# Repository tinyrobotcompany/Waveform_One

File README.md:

# Waveform One

A music-reactive 64×32 HUB75 LED display with a touchscreen and local phone
remote. The current P4 configuration uses the Waveshare
ESP32-P4-WIFI6-Touch-LCD-7B, onboard ES7210 audio capture and direct P4 LED drive.
It joins home Wi-Fi and uses ACRCloud for music identification. The retired Raspberry Pi runtime and its release artifacts have been removed.
Standalone S3 hardware test programs remain for bench testing.

Public source and local audio processing are foundations for long-term ownership.
Cloud song identification still requires ACRCloud. A repeatable recognition
accuracy benchmark and a documented cold-boot offline demonstration are pending;
see the evidence and acceptance plans below rather than assuming a measured
accuracy percentage or a complete offline guarantee.

## Licence and independent maintenance

Original software is licensed under [Apache 2.0](LICENSE). Original hardware and mechanical designs are licensed under [CERN-OHL-W 2.0](LICENSES/CERN-OHL-W-2.0.txt). See [licensing scope and third-party exclusions](LICENSING.md). These licences allow independent maintenance and commercial use; they do not provide recognition-service accounts or rights to our trademarks.

## Documentation

- [Wiring, firmware programs and build instructions](firmware/esp32/README.md)
- [ESP32-P4 display bring-up and wiring](firmware/esp32/p4_display/README.md)
- [ESP32-P4 controller architecture decision](docs/architecture/0001-esp32-p4-display-controller.md)
- [Contributing and local tests](CONTRIBUTING.md)
- [Release notes](CHANGELOG.md)
- [Native P4 over-the-air updates](docs/p4-ota.md)
- [Recognition accuracy protocol and result template](docs/validation/recognition-protocol.md)
- [Recognition providers and commercial-cost review](docs/product/recognition-commercial-review.md)
- [Offline visualizer acceptance plan](docs/validation/offline-visualizer.md)
- [Ownership and service continuity](docs/product/longevity.md)
- [Buyer-readiness checklist](https://github.com/tinyrobotcompany/Waveform_One/issues/25)
- [CI and releases](docs/delivery.md)
- [Wi-Fi and QR phone setup](docs/setup.md)
- [HTTPS identity provisioning and renewal](docs/secure-phone-access.md)
- [Managed certificate migration plan and accepted decisions](docs/plans/managed-certificates.md)
- [Agent in Chief working protocol](docs/engineering-agent-protocol.md)
- [Production secure boot and encrypted credentials](docs/production-security.md)

Native P4 signed updates follow Tempo: monthly checks, an overnight installation
window, countdown and postponement, with controls on the touchscreen and paired phone.
The P4 needs a one-time USB bootstrap into the A/B layout before OTA updates.

<!-- privacy-notice:start -->
## Microphone and privacy

**Waveform One does not save audio recordings on the device.** Automatic music
recognition is a core feature and runs during normal operation. This notice
describes the current ESP32-P4 firmware; temporary audio capture and transmission
for recognition are different from saving a permanent recording.

**What the microphone captures.** While powered on and running with capture enabled,
the microphone continuously captures nearby sound to animate the LEDs and identify music. Audio
is processed in temporary RAM, including a rolling 16-second buffer. Buffers are
reused; this is not a recording archive or a guarantee that every temporary copy
is securely erased after exactly 16 seconds. Waveform One does not provide
conversation transcription or a feature for replaying recorded conversations.

**What leaves the device.** For recognition, the P4 sends actual audio clips of
up to 10 seconds directly to ACRCloud over HTTPS, not to a Waveform One audio-storage
server. Requests can repeat approximately every 2.5 seconds while recognition is
active, so clips overlap substantially. Requests also include an account access-key
identifier, request timestamp and authentication signature; the service can see
the connecting network's public IP address. The access secret is used locally to
sign requests, rather than sent as an audio-request field.

**Nearby voices.** Clips may include nearby voices and other background sounds.
Sound classification cannot guarantee that speech is excluded, and sustained
unclassified sound can also trigger a recognition request. Do not assume that
only music leaves the device. People nearby should be made aware that automatic
music recognition can send samples containing their voices to ACRCloud.

**Provider processing and retention.** ACRCloud states that temporary raw audio
is deleted when request processing succeeds or fails, without a retained audio
archive or long-term audio backup. Recognition results, fingerprints, request
records and technical logs have separate retention and deletion rules; they are
not all deleted with the audio. Processing location depends on the ACRCloud
project's configured region. See [ACRCloud's data-processing terms](https://www.acrcloud.com/dpa/)
and [privacy policy](https://www.acrcloud.com/privacy/). These are the
provider's commitments, not a claim that Waveform One independently verifies
server-side deletion. Requests about provider-held data should follow the
applicable account's ACRCloud privacy and deletion procedures.

**Other stored information.** Device diagnostics include recognised titles,
artists, timings and sound levels, and can be retained when captured by a
connected development computer. Recognition metadata and artwork may be cached
for display. ACRCloud credentials are stored on the device so recognition
continues after firmware updates; that credential storage is separate from audio
buffering. Using your own ACRCloud account changes whose account is used, not
whether recognition audio is transmitted to ACRCloud.

**Optional listening history and sharing.** On firmware offering listening history,
collection starts disabled after every restart. Enabling it stores up to 50 recent
recognised tracks and timing metadata in device RAM; it stores no audio. Paired
phones can view, export or delete this history. Disabling it or restarting clears
the device history, but does not delete exported files. The optional desktop
Last.fm bridge sends eligible track metadata and timestamps only after the owner
authorises their account and explicitly submits an export. It stores account
credentials and a bounded submission queue on that computer with private file
permissions, without encryption. Deleting local files does not delete Last.fm's
records; use Last.fm's account controls. Discogs links open a search only when
clicked and disclose the search terms and normal browser/network information to
Discogs. Neither integration uploads microphone audio.

**Owner account controls.** On firmware offering owner account setup, credentials
are entered on the touchscreen, not through the phone's unencrypted local HTTP
connection. Replacing or disabling an account takes effect after restart; recognition
can continue with the previous account until then. Disabling the account stops
cloud recognition after restart but leaves local microphone processing active.
Wi-Fi/pairing/account settings persist in device storage, which is not newly
encrypted by these features. Removal is not a claim of forensic secure erasure.

**Stopping capture.** Powering off Waveform One stops microphone capture and
uploads. Disconnecting its internet connection prevents cloud recognition
requests from reaching ACRCloud, but does not itself turn off the microphone.
On firmware with Settings → Microphone, the touchscreen mute pauses local P4
capture, clears capture buffers, invalidates old audio/results and inhibits new
recognition requests. The paired phone shows the muted state. A successfully
saved mute survives normal restart and application OTA; an erased/reset settings
partition restores the fresh-device default of listening. If saving fails, mute
still takes effect now, but the screen warns that the previous saved setting may
return after restart. Unmute requires a successful save; corrupt/unreadable
settings default to muted without erasing storage.

This is a software mute: the microphones remain electrically connected and may
remain powered. It is not a physical privacy switch or a guarantee against
replacement/malicious firmware. Microphone-reactive LEDs also stop receiving
sound while muted. An already-running capture read is discarded when it returns;
an in-progress network operation may finish before cancellation is observed.
Cancelled uploads are closed and not retried, but bytes already sent cannot be
recalled. No switch installation, GPIO wiring or microphone modification is
required. The control covers the local P4 capture path, not a separately running
legacy S3 microphone controller.
<!-- privacy-notice:end -->

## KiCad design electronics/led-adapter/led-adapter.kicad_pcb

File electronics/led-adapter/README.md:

# LED adapter board

A small board (94 × 44 mm) that connects the P4 touchscreen board to the LED
panel, so the P4 can drive the panel without the ESP32-S3 and without loose
jumper wires. It is also the system's one power point: the 5 V supply plugs in
here, and the board powers the LED panel and the P4. Every cable plugs in at
both ends.

```text
5 V supply (barrel plug) ── J5 ┬── J4 ──[panel's own power cable]── LED panel power
                               ├── J6 ──[USB-C to USB-C cable]────── P4 USB-C port
                               └── buffers, power LED
P4 socket P3 ──[PH2.0 12-pin cable, as delivered]── J1 ┐
                                                       ├─ buffers ── J3 ──[panel's grey ribbon]── LED panel input
P4 socket P1 ──[PH2.0 12-pin cable, as delivered]── J2 ┘
```

| Connector | Takes |
|---|---|
| J1 | Cable to the P4's **P3** socket (GPIO2–5, 28–31, 34; 3.3 V and GND) |
| J2 | Cable to the P4's **P1** socket (GPIO49–52; GND) |
| J3 | The LED panel's own 16-pin ribbon (HUB75) |
| J4 | The LED panel's own power cable (screw terminal, up to 4 A) |
| J5 | The 5 V supply's barrel plug (5.5 × 2.1 mm, centre +) |
| J6 | USB-C to USB-C cable to the P4's USB-C port (power only) |

The labels are printed on the board. D2, marked POWER, lights while 5 V is
present.

## In the case

The board lies flat on four floor posts (M3 heat-set inserts, 5 mm high) in
the left half, behind the screen and under the P4's two 12-pin sockets, with
J1 and J2 towards the back. `board.json` gives its position (`case_left_x`,
`case_rear_y`, `standoff_height`); the casing CAD reads it from
`placement.json`, as it does for the carrier board.

## What is on it

- **One power input, J5**, for a 5 V supply of at least 6 A: up to 4 A for
  the panel and the rest for the P4. MEAN WELL GST60A05-P1J (5 V, 6 A,
  5.5 × 2.1 mm plug, centre +) fits. A TVS diode (D1) clamps plug-in spikes.
- **The panel's power, J4**, straight from J5 on wide copper.
- **The P4's power, J6**, through a 2.5 A resettable fuse (F1). Waveshare
  documents USB-C (or a battery) as the P4's only power inputs, so the board
  feeds it like a USB charger: 56 kΩ on CC1 and CC2 mark it as a USB power
  source. The P4's two USB-C ports each have their own input diode, so the
  Mac can stay plugged into the P4's other USB-C port for flashing.
- **Two 74AHCT245 buffers** turn the P4's 3.3 V signals into the 5 V the
  panel expects. These are the same buffers as on the carrier board.
- **The panel stays dark unless the P4 is on.** Q1 enables the buffers only
  while the P4's 3.3 V is present. Otherwise R4 holds the panel's OE high.
  R1 does the same while the P4 starts.

The signal map is Codex's, from
`docs/commissioning/2026-10-14-p4-led-takeover.md`:

| HUB75 | R1 | G1 | B1 | R2 | G2 | B2 | A | B | C | D | CLK | LAT | OE |
|---|---|---|---|---|---|---|---|---|---|---|---|---|---|
| P4 GPIO | 2 | 3 | 4 | 5 | 28 | 29 | 30 | 31 | 34 | 49 | 52 | 50 | 51 |

The P4's socket pins come from Waveshare's 7B schematic (P1 and P3).
`tools/netlist.py` lists them pin by pin.

## Cables

### The two 12-pin cables: use them as delivered

J1 and J2 take PH2.0 12-pin double-ended cables **exactly as they come from
the bag**: the AliExpress "Double head, 12P, 20CM" cables. Don't move any wire.

Those cables are crossed: pin 1 at one end is wired to pin 12 at the other.
Revision 2 makes the cross-over on the board instead. J1 and J2 pin *n*
carries the P4 socket's pin 13 − *n*:

| P4 P3 pin | P3 label | J1 pin | | P4 P1 pin | P1 label | J2 pin |
|---|---|---|---|---|---|---|
| 1 | IO36 | 12 (unused) | | 1 | IO52 (CLK) | 12 |
| 2 | IO34 (C) | 11 | | 2 | IO51 (OE) | 11 |
| 3 | IO31 (B) | 10 | | 3 | IO50 (LAT) | 10 |
| 4 | IO30 (A) | 9 | | 4 | IO49 (D) | 9 |
| 5 | IO29 (B2) | 8 | | 5–7 | IO48–46 | 8–6 (unused) |
| 6 | IO28 (G2) | 7 | | 8 | GND | 5 |
| 7 | IO5 (R2) | 6 | | 9 | VO4 | 4 (unused) |
| 8 | IO4 (B1) | 5 | | 10 | 3V3 | 3 (unused) |
| 9 | IO3 (G1) | 4 | | 11 | GND | 2 |
| 10 | IO2 (R1) | 3 | | 12 | BAT | 1 (unused) |
| 11 | GND | 2 | | | | |
| 12 | 3V3 | 1 | | | | |

How we know: the owner's photos of the cables plugged in unmodified
(2026-11-04). At the P4's P3 socket, from IO36 to 3V3, the wires run red,
black, brown, grey, purple, blue, green, orange, yellow, white, red, black.
At revision 1's J1, from pin 1 (the end nearest J4) to pin 12, they ran in
exactly the opposite order. The P1 cable is the same.

**Check before plugging in: follow each cable, don't go by colour.** The two
cables are identical, with the same colours, so a cable plugged into the
wrong board socket looks just like a right one. Trace each cable by hand from
end to end:

- from the P4's **P3** socket (pins labelled 3V3, GND, IO2 … IO36) to **J1**,
  printed "to P4 socket P3";
- from the P4's **P1** socket (pins labelled BAT, GND, 3V3, VO4 … IO52) to
  **J2**, printed "to P4 socket P1".

The cables themselves are never modified. In the working setup (photo,
2026-11-17) the two cables cross over each other between the P4 and the
green board: that crossing is what puts each cable in its own socket. If the
two cables run side by side without crossing, check them again.

If the two cables are in each other's sockets at the green board, the POWER
LED lights and the P4 starts, but the panel stays dark. Swap the two plugs at
the green board, without changing the cables. (This happened at the first revision 2 bring-up,
2026-11-17; after the swap the panel worked with the cables as delivered.)
Don't leave them swapped: J1 pin 1, the board's 3.3 V input, then gets the
P4's BAT pin.

The two cables reworked by hand for revision 1 (wires moved to run pin 1 to
pin 1) do **not** work on revision 2. Keep them with the revision 1 board.

### Power

- **5 V supply**: 5 V, at least 6 A, barrel plug 5.5 × 2.1 mm, centre +. For
  example MEAN WELL GST60A05-P1J (it needs an IEC C13 mains lead, sold
  separately).
- **USB-C to USB-C cable**, short (about 20 cm), from J6 to the P4's USB-C
  port. Any charging cable works: only power goes through it.
- **The panel's own power cable** into J4: red to **+5V**, black to **GND**,
  as printed.

### Panel signals

- The panel's grey 16-pin ribbon, which came with the panel, into J3 and the
  panel's **input** socket.

## Order from JLCPCB

```sh
python3 electronics/led-adapter/tools/export_jlc.py
```

This writes `fab/`. On jlcpcb.com, follow the carrier board's steps
(`electronics/carrier/README.md`, "Order from JLCPCB"):

1. Upload `led-adapter-gerbers.zip`. Use the defaults: 2 layers, 1.6 mm,
   quantity 5.
2. Turn on PCB Assembly, top side. J1–J5 are through-hole, so choose
   **Standard** assembly with through-hole soldering.
3. Upload `led-adapter-bom.csv` and `led-adapter-cpl.csv`. Check that every
   part is matched and in stock.
4. In the placement preview, check that each part sits the right way round.
   Compare it with KiCad's render (`kicad-cli pcb render --side top`):
   - pin 1 of U1, U2, Q1, D1, D2, J1, J2 and J3;
   - the wire entries of J4, which face the board's front edge (away from the
     "+5V" and "GND" text), so the wires come in from the front as the case
     expects;
   - the plug opening of J5, at the board's rear edge (next to J1), and the
     mouth of J6, at the board's left edge.

   Rotate any part that is wrong in JLCPCB's preview. Revision 1 was ordered
   with J4 turned the other way, and JLCPCB was asked to turn it 180° (2026-10-20);
   these files now have it the right way round.

## Regenerate

The tools reuse the carrier board's generators (`reuse.py` points them at this
folder). Don't edit the generated files by hand. Edit `tools/netlist.py` or
`board.json` instead, then run:

```sh
python3 electronics/led-adapter/tools/gen_schematic.py
KP=/Applications/KiCad/KiCad.app/Contents/Frameworks/Python.framework/Versions/Current/bin/python3
$KP electronics/led-adapter/tools/build_board.py
$KP electronics/led-adapter/tools/route_board.py      # needs Java and Freerouting, as for the carrier
K=/Applications/KiCad/KiCad.app/Contents/MacOS/kicad-cli
$K sch erc electronics/led-adapter/led-adapter.kicad_sch
$K pcb drc --schematic-parity electronics/led-adapter/led-adapter.kicad_pcb
```

## Status

- **Revision 2** (this design): one power point, power LED, cables used as
  delivered. Designed, routed and checked: no design-rule violations,
  nothing unconnected, and the board matches the schematic. Every panel
  signal was traced from the P4 pin, through an as-delivered cable, to the
  HUB75 pin. **Ordered 2026-11-14** from JLCPCB, 5 assembled boards
  (order Y4-13817483A). J6 was fitted as LCSC C3020560, the same GCT
  USB4105-GF-A, because C3025063 was out of stock.
  **Working on hardware 2026-11-17**: P4 powered from J6 and the panel
  lit, with both 12-pin cables as delivered.
- **Revision 1** (ordered 2026-10-20, in use): needs the 12-pin cables
  reworked to run pin 1 to pin 1, takes 5 V for the buffers only on J4, and
  the P4 is powered separately by USB-C.
- Revision 2 is 22 mm wider on the left than revision 1; the parts from
  revision 1 sit at the same places in the case. The casing CAD follows
  `placement.json`: rebuild the case before printing it for revision 2.

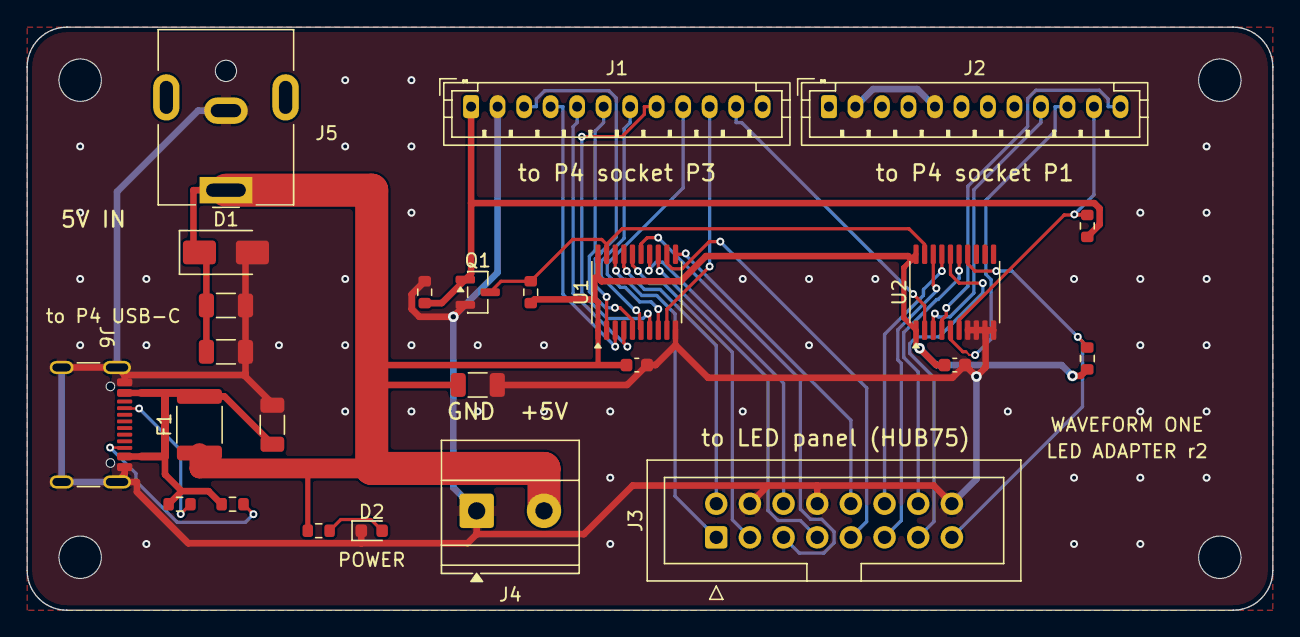
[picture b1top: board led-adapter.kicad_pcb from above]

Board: 2 copper layers, 94.0 x 44.0 mm, 29 parts (0 on the bottom side), 34 nets.

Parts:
C1, C2: 100nF; C_0603_1608Metric
C3, C4, C5, C6: 22uF 10V; C_1206_3216Metric
D1: SMAJ5.0A; D_SMA
D2: Green; LED_0603_1608Metric
F1: 2.5A hold; Fuse_1812_4532Metric
H1, H2, H3, H4: M3; MountingHole_3.2mm_M3
J1, J2: PH2.0 12-pin; JST_PH_B12B-PH-K_1x12_P2.00mm_Vertical
J3: HUB75; IDC-Header_2x08_P2.54mm_Vertical
J4: 5V to LED panel; TerminalBlock_Phoenix_MKDS-1,5-2-5.08_1x02_P5.08mm_Horizont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
J5: PJ-063AH; BarrelJack_CUI_PJ-063AH_Horizontal
J6: 5V to P4; USB_C_Receptacle_GCT_USB4105-xx-A_16P_TopMnt_Horizontal
Q1: 2N7002; SOT-23
R1, R3, R4: 10k; R_0603_1608Metric
R2: 100k; R_0603_1608Metric
R5, R6: 56k; R_0603_1608Metric
R7: 1k; R_0603_1608Metric
U1, U2: 74AHCT245; TSSOP-20_4.4x6.5mm_P0.65mm

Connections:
/+5V: C1.1, C2.1, C3.1, C4.1, C5.1, D1.1, F1.1, J4.2, J5.1, R3.1, R4.1, R7.1, U1.1, U1.20, U2.1, U2.20
/BUF_EN: Q1.3, R3.2, U1.19, U2.19
/GND: C1.2, C2.2, C3.2, C4.2, C5.2, C6.2, D1.2, D2.1, J1.2, J2.2, J2.5, J3.4, J3.8, J3.16, J4.1, J5.2, J6.A1, J6.A12, J6.B1, J6.B12, J6.SH, Q1.2, R2.2, U1.10, U2.7, U2.8, U2.9, U2.10
/HUB_A: J3.9, U1.12
/HUB_B: J3.10, U1.11
/HUB_B1: J3.3, U1.16
/HUB_B2: J3.7, U1.13
/HUB_C: J3.11, U2.18
/HUB_CLK: J3.13, U2.16
/HUB_D: J3.12, U2.17
/HUB_G1: J3.2, U1.17
/HUB_G2: J3.6, U1.14
/HUB_LAT: J3.14, U2.15
/HUB_OE: J3.15, R4.2, U2.14
/HUB_R1: J3.1, U1.18
/HUB_R2: J3.5, U1.15
/LED_5V: D2.2, R7.2
/P4_3V3: J1.1, Q1.1, R1.1, R2.1
/P4_5V: C6.1, F1.2, J6.A4, J6.A9, J6.B4, J6.B9, R5.1, R6.1
/P4_A: J1.9, U1.8
/P4_B: J1.10, U1.9
/P4_B1: J1.5, U1.4
/P4_B2: J1.8, U1.7
/P4_C: J1.11, U2.2
/P4_CC1: J6.A5, R5.2
/P4_CC2: J6.B5, R6.2
/P4_CLK: J2.12, U2.4
/P4_D: J2.9, U2.3
/P4_G1: J1.4, U1.3
/P4_G2: J1.7, U1.6
/P4_LAT: J2.10, U2.5
/P4_OE: J2.11, R1.2, U2.6
/P4_R1: J1.3, U1.2
/P4_R2: J1.6, U1.5

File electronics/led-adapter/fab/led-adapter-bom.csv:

Comment,Designator,Footprint,LCSC Part #
PH2.0 12-pin,"J1,J2",JST_PH_B12B-PH-K_1x12_P2.00mm_Vertical,C158028
10k,"R1,R3,R4",R_0603_1608Metric,C25804
2N7002,Q1,SOT-23,C8545
100k,R2,R_0603_1608Metric,C25803
74AHCT245,"U1,U2",TSSOP-20_4.4x6.5mm_P0.65mm,C173388
100nF,"C1,C2",C_0603_1608Metric,C14663
HUB75,J3,IDC-Header_2x08_P2.54mm_Vertical,C492443
5V to LED panel,J4,"TerminalBlock_Phoenix_MKDS-1,5-2-5.08_1x02_P5.08mm_Horizontal",C480516
PJ-063AH,J5,BarrelJack_CUI_PJ-063AH_Horizontal,C22434582
SMAJ5.0A,D1,D_SMA,C78401
22uF 10V,"C3,C4,C5,C6",C_1206_3216Metric,C12891
1k,R7,R_0603_1608Metric,C21190
Green,D2,LED_0603_1608Metric,C12624
2.5A hold,F1,Fuse_1812_4532Metric,C19078727
5V to P4,J6,USB_C_Receptacle_GCT_USB4105-xx-A_16P_TopMnt_Horizontal,C3025063
56k,"R5,R6",R_0603_1608Metric,C23206

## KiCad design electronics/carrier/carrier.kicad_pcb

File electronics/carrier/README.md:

# Carrier board

The board inside the cabinet that carries the ESP32-S3, drives the LED panel,
connects the microphone and shares out power. See [SPEC.md](SPEC.md).

Designed in KiCad 10. Placement is generated from `board.json`, which is the
single source for the outline, mounting holes and connector positions. The
casing CAD reads the same file.

## Rebuild the board placement

```sh
/Applications/KiCad/KiCad.app/Contents/Frameworks/Python.framework/Versions/Current/bin/python3 \
    electronics/carrier/tools/build_board.py
```

## Route

```sh
/Applications/KiCad/KiCad.app/Contents/Frameworks/Python.framework/Versions/Current/bin/python3 \
    electronics/carrier/tools/route_board.py
```

Needs Java and Freerouting 2.4.1 (`FREEROUTING_JAR`). It replaces all copper:
it draws the fixed tracks in `route_board.py`, autoroutes the rest, pours
ground and stitches it, and reports what is left unconnected. Rerun it after
every `build_board.py`.

## Order from JLCPCB

```sh
python3 electronics/carrier/tools/export_jlc.py
```

This writes `fab/`: `carrier-gerbers.zip` (the board), `carrier-bom.csv`
(parts with LCSC numbers, from `LCSC` in `netlist.py`) and `carrier-cpl.csv`
(part positions). Not-fitted parts are left out. On jlcpcb.com:

1. Upload `carrier-gerbers.zip`. Keep the defaults: 2 layers, 1.6 mm,
   1 oz copper, HASL lead-free (or ENIG), quantity 5.
2. Turn on PCB Assembly: top side, assemble 5 boards. The through-hole
   connectors (J1, J4, J5, J6) need Standard assembly with through-hole
   soldering, not Economic.
3. Upload `carrier-bom.csv` and `carrier-cpl.csv`. Check every part is
   matched and in stock.
4. In the placement preview, check each polarised part sits the right way
   round: pin 1 of U1, U4, U5, U6, U7 and J7; the stripe of D1; the green LED
   D2; the + of C1; and that each connector faces the board edge it should.
   JLCPCB's part models can be rotated from KiCad's; rotate any that are
   wrong there.

## Check and preview

```sh
K=/Applications/KiCad/KiCad.app/Contents/MacOS/kicad-cli
$K pcb drc --severity-all -o /tmp/carrier-drc.txt electronics/carrier/carrier.kicad_pcb
$K pcb render --side top -o /tmp/carrier-top.png electronics/carrier/carrier.kicad_pcb
```

## Design source

`tools/netlist.py` holds the circuit: every part, value, footprint and pin net.
Two generators read it:

- `tools/gen_schematic.py` writes `carrier.kicad_sch`. Any Python 3.9+ runs it.
- `tools/build_board.py` writes `carrier.kicad_pcb`, with every pad on its net,
  and `placement.json`. It needs KiCad's Python.

Do not edit the generated files by hand. Change `netlist.py`, `board.json` or
the fixed copper in `route_board.py` and regenerate:

```sh
python3 electronics/carrier/tools/gen_schematic.py
KP=/Applications/KiCad/KiCad.app/Contents/Frameworks/Python.framework/Versions/Current/bin/python3
$KP electronics/carrier/tools/build_board.py
$KP electronics/carrier/tools/route_board.py
K=/Applications/KiCad/KiCad.app/Contents/MacOS/kicad-cli
$K sch erc electronics/carrier/carrier.kicad_sch
$K pcb drc --schematic-parity electronics/carrier/carrier.kicad_pcb
```

## Status

Revision 1 is placed and routed.

- Schematic: passes the electrical rules check. The only warnings are the
  three intentional ties of unused buffer inputs to ground.
- Board: matches the schematic exactly, and passes the design-rule check with
  no errors and nothing unconnected. Four warnings remain: the silkscreen
  outlines of the USB-A socket (J4) and the LED power terminal (J6) overhang
  the board edge, as those connectors do by design. A fifth flags that the
  S3 module's footprint differs from KiCad's library: its ground-pad holes
  are drilled 0.3 mm instead of 0.2 mm, so every hole on the board is a
  standard drill size at JLCPCB.
- Chip resistor and capacitor references are left off the silkscreen (too
  dense); they remain on the fabrication layer.
- The USB-C power parts are marked do-not-populate. Their layout is complete
  but provisional; see SPEC.md before fitting them.

Library warnings in `kicad-cli` mean KiCad's global library tables are not set
up yet. Opening KiCad once creates them.

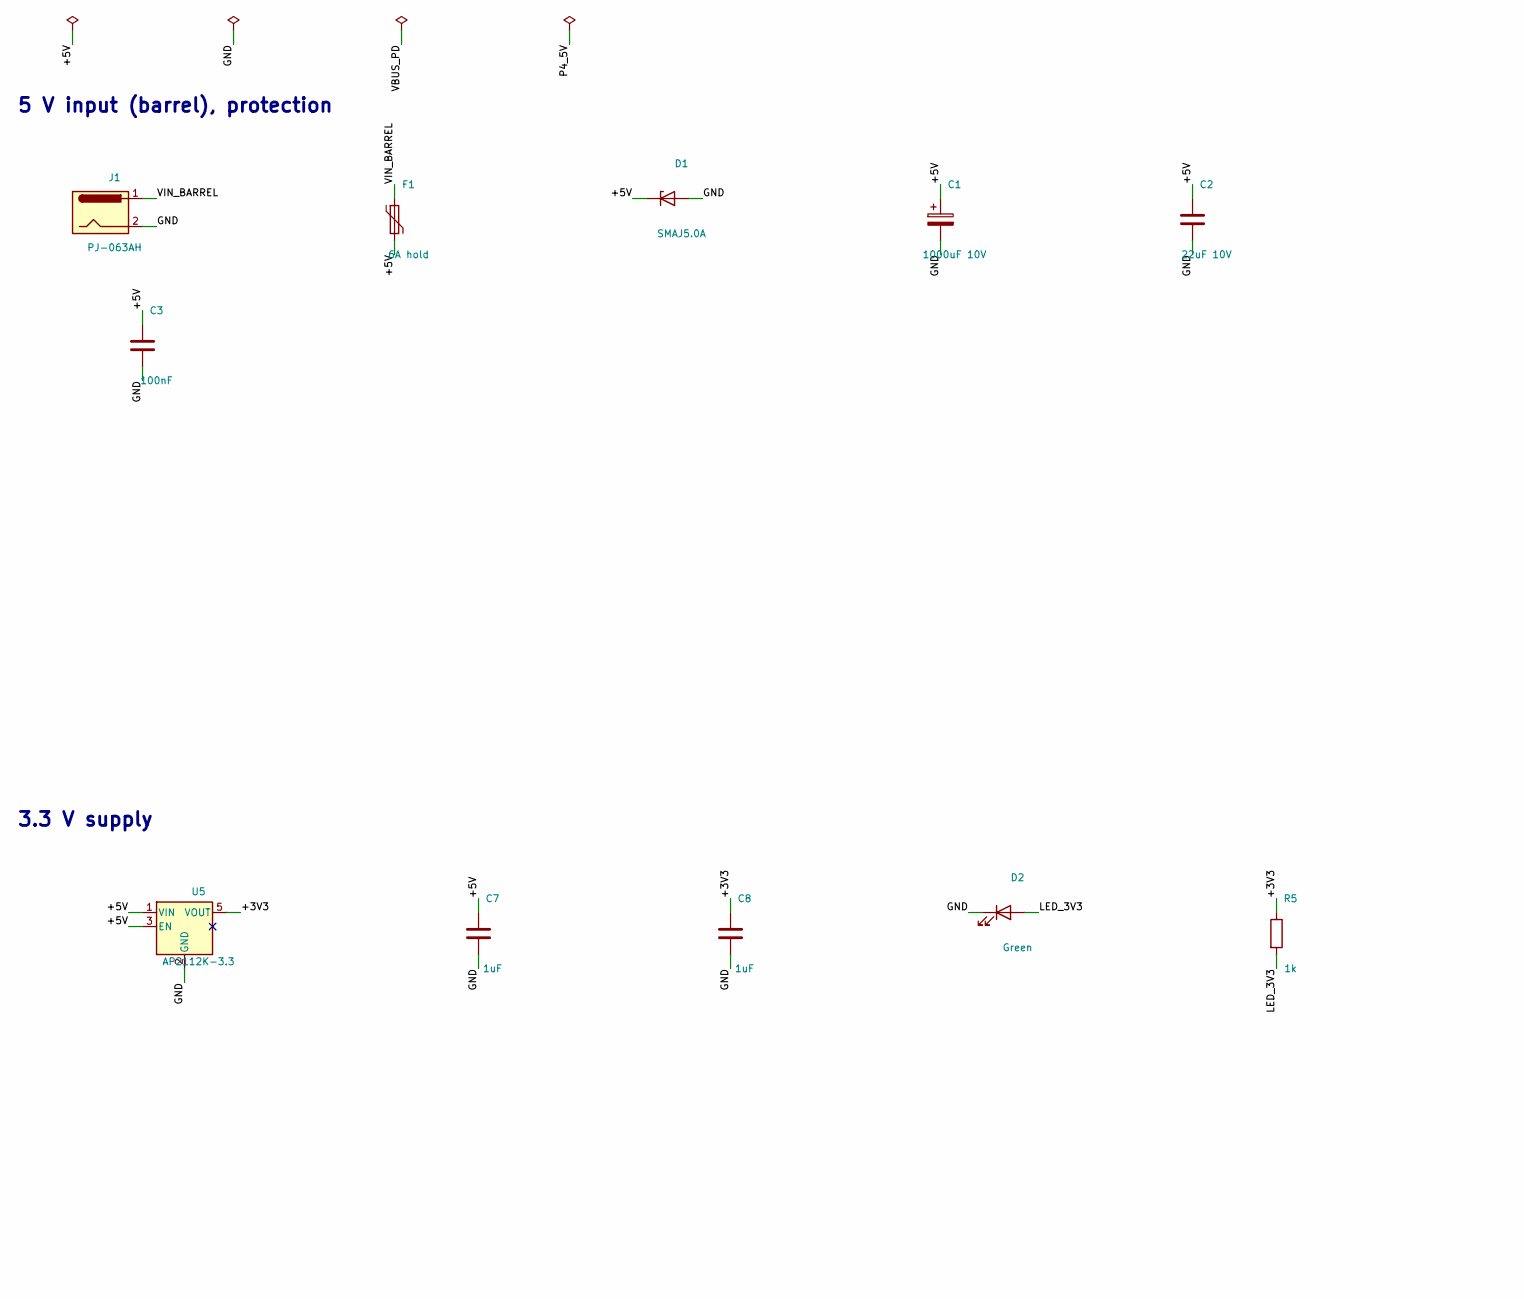
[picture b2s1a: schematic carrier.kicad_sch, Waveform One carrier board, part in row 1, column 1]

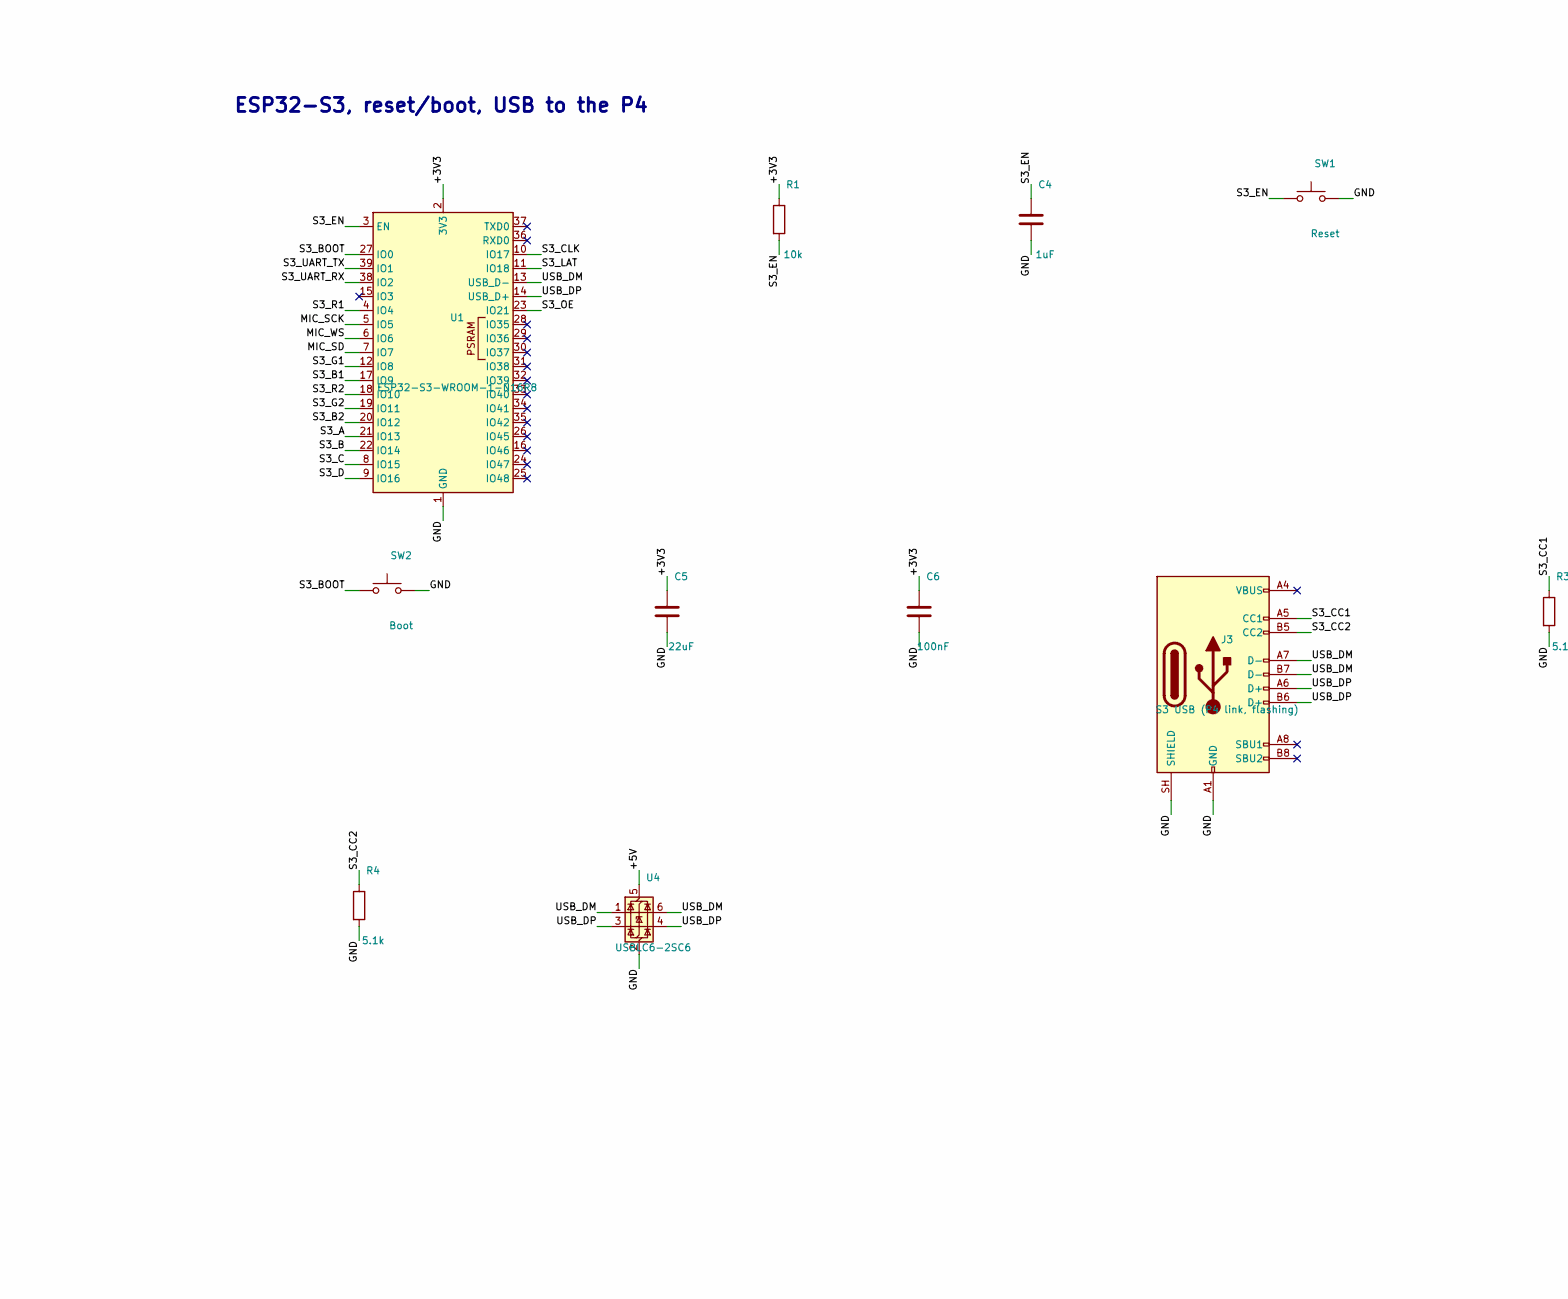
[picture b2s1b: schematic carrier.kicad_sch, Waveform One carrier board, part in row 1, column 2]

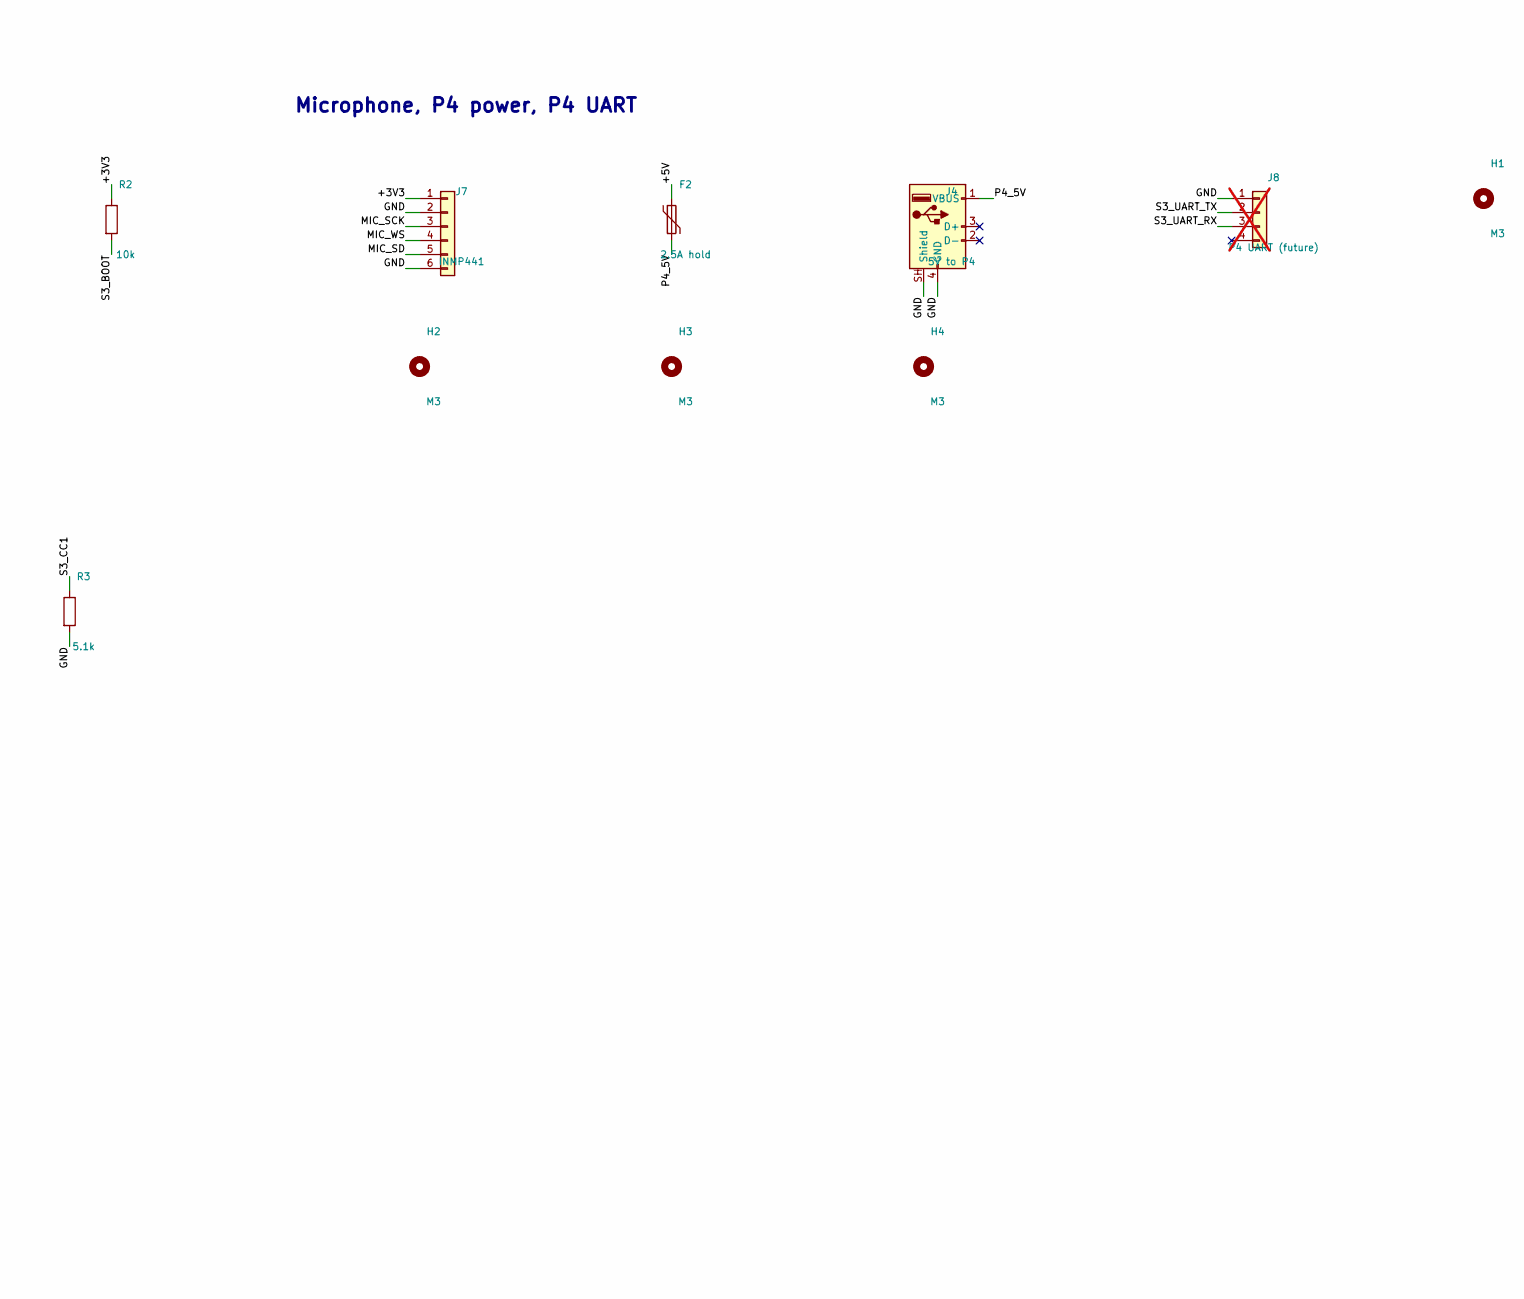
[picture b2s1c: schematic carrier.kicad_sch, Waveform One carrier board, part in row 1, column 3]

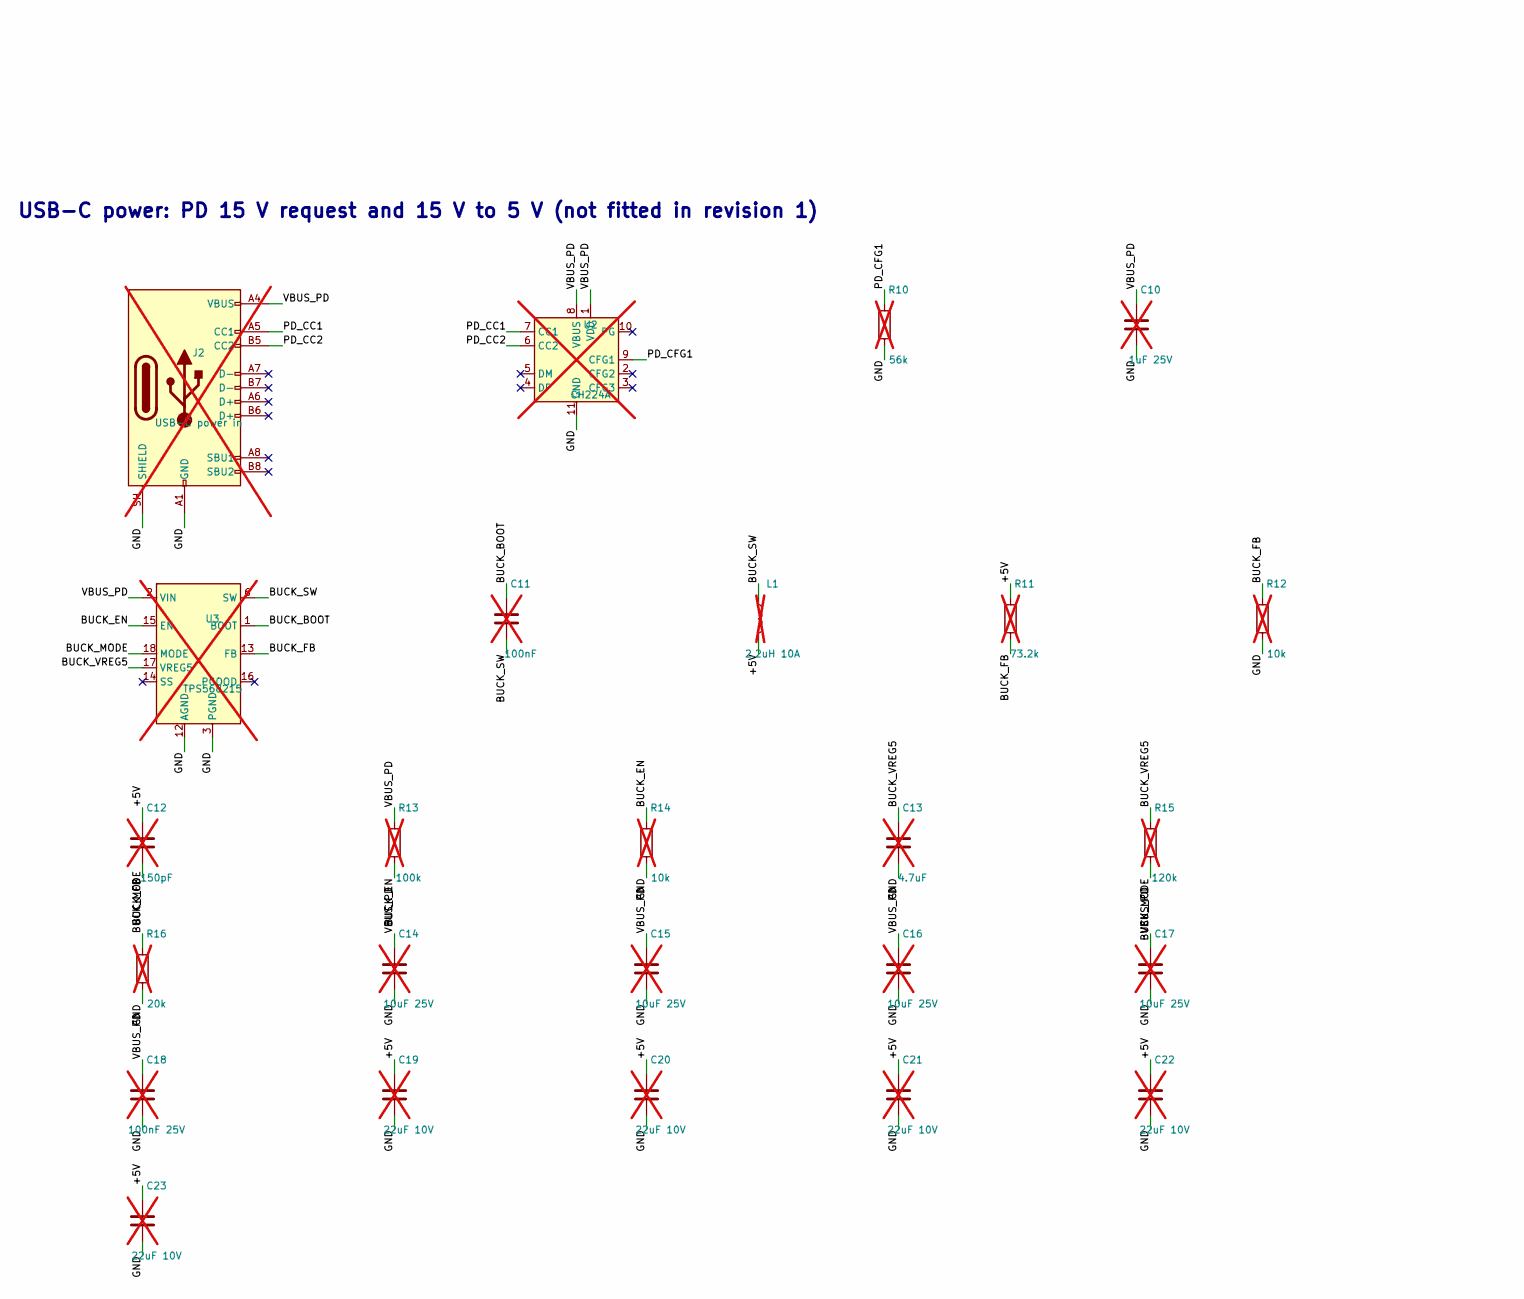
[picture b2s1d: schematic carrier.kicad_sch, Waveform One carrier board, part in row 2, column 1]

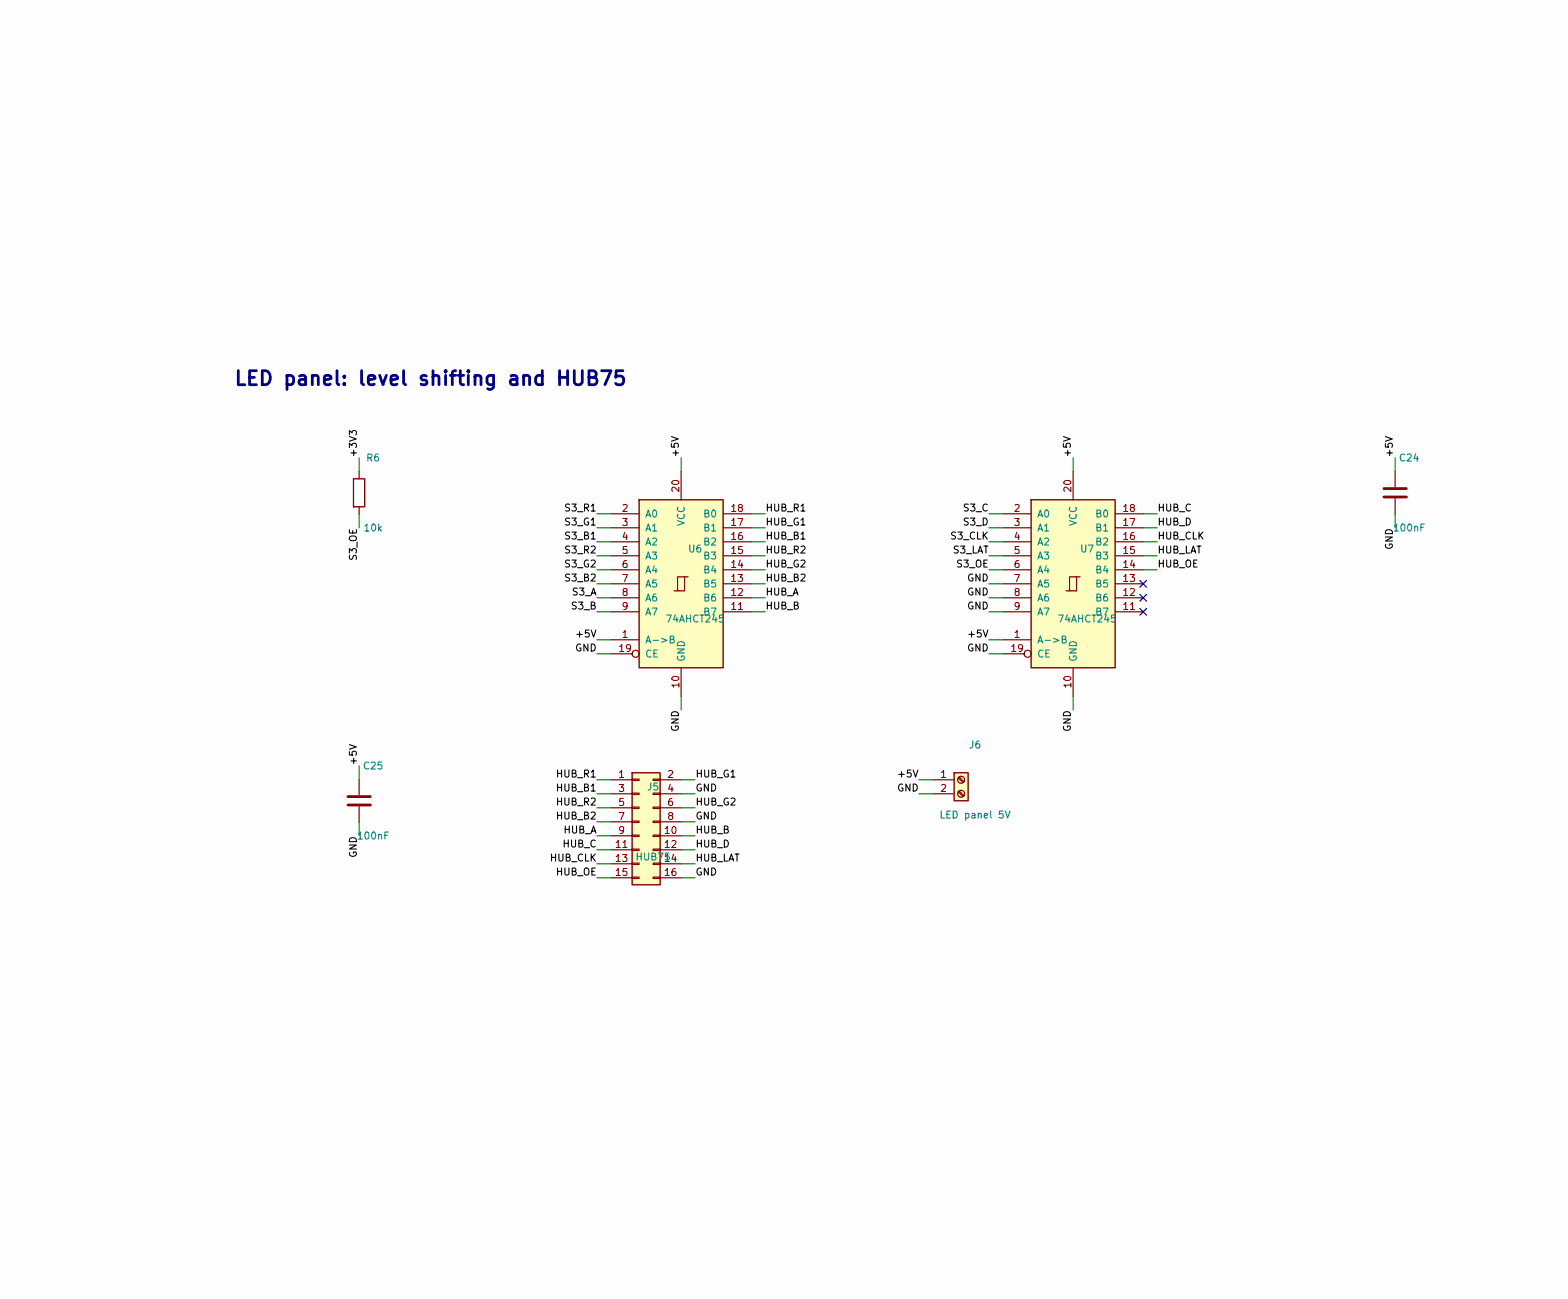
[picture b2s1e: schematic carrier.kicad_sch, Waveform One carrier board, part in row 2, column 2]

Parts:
C1: 1000uF 10V; CP_Elec_10x10.5
C2: 22uF 10V; C_1206_3216Metric
C3, C6, C24, C25: 100nF; C_0603_1608Metric
C4, C7, C8: 1uF; C_0603_1608Metric
C5: 22uF; C_1206_3216Metric
C10: 1uF 25V; C_0805_2012Metric; not fitted
C11: 100nF; C_0603_1608Metric; not fitted
C12: 150pF; C_0603_1608Metric; not fitted
C13: 4.7uF; C_0805_2012Metric; not fitted
C14, C15, C16, C17: 10uF 25V; C_1206_3216Metric; not fitted
C18: 100nF 25V; C_0603_1608Metric; not fitted
C19, C20, C21, C22, C23: 22uF 10V; C_1206_3216Metric; not fitted
D1: SMAJ5.0A; D_SMA
D2: Green; LED_0603_1608Metric
F1: 6A hold; Fuse_2920_7451Metric
F2: 2.5A hold; Fuse_1812_4532Metric
H1, H2, H3, H4: M3; MountingHole_3.2mm_M3
J1: PJ-063AH; BarrelJack_CUI_PJ-063AH_Horizontal
J2: USB-C power in; USB_C_Receptacle_HRO_TYPE-C-31-M-12; not fitted
J3: S3 USB (P4 link, flashing); USB_C_Receptacle_GCT_USB4105-xx-A_16P_TopMnt_Horizontal
J4: 5V to P4; USB_A_Molex_67643_Horizontal
J5: HUB75; IDC-Header_2x08_P2.54mm_Vertical
J6: LED panel 5V; TerminalBlock_Phoenix_MKDS-1,5-2-5.08_1x02_P5.08mm_Horizont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
J7: INMP441; JST_GH_BM06B-GHS-TBT_1x06-1MP_P1.25mm_Vertical
J8: P4 UART (future); JST_PH_B4B-PH-K_1x04_P2.00mm_Vertical; not fitted
L1: 2.2uH 10A; L_Coilcraft_XAL7070-XXX; not fitted
R1, R2, R6: 10k; R_0603_1608Metric
R3, R4: 5.1k; R_0603_1608Metric
R5: 1k; R_0603_1608Metric
R10: 56k; R_0603_1608Metric; not fitted
R11: 73.2k; R_0603_1608Metric; not fitted
R12, R14: 10k; R_0603_1608Metric; not fitted
R13: 100k; R_0603_1608Metric; not fitted
R15: 120k; R_0603_1608Metric; not fitted
R16: 20k; R_0603_1608Metric; not fitted
SW1: Reset; SW_SPST_TL3342
SW2: Boot; SW_SPST_TL3342
U1: ESP32-S3-WROOM-1-N16R8; ESP32-S3-WROOM-1
U2: CH224A; SSOP-10-1EP_3.9x4.9mm_P1mm_EP2.1x3.3mm; not fitted
U3: TPS568215; Texas_RNN0018A; not fitted
U4: USBLC6-2SC6; SOT-23-6
U5: AP2112K-3.3; SOT-23-5
U6, U7: 74AHCT245; TSSOP-20_4.4x6.5mm_P0.65mm

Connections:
/+3V3: C5.1, C6.1, C8.1, J7.1, R1.1, R2.1, R5.1, R6.1, U1.2 (3V3), U5.5 (VOUT)
/+5V: C1.1, C2.1, C3.1, C7.1, C12.1, C19.1, C20.1, C21.1, C22.1, C23.1, C24.1, C25.1, D1.1 (K), F1.2, F2.1, J6.1, L1.2, R11.1, U4.5 (VBUS), U5.1 (VIN), U5.3 (EN), U6.1 (A->B), U6.20 (VCC), U7.1 (A->B), U7.20 (VCC)
/BUCK_BOOT: C11.1, U3.1 (BOOT)
/BUCK_EN: R13.2, R14.1, U3.15 (EN)
/BUCK_FB: C12.2, R11.2, R12.1, U3.13 (FB)
/BUCK_MODE: R15.2, R16.1, U3.18 (MODE)
/BUCK_SW: C11.2, L1.1, U3.6 (SW), U3.7 (SW)
/BUCK_VREG5: C13.1, R15.1, U3.17 (VREG5)
/GND: C1.2, C2.2, C3.2, C4.2, C5.2, C6.2, C7.2, C8.2, C10.2, C13.2, C14.2, C15.2, C16.2, C17.2, C18.2, C19.2, C20.2, C21.2, C22.2, C23.2, C24.2, C25.2, D1.2 (A), D2.1 (K), J1.2, J2.A1 (GND), J2.A12 (GND), J2.B1 (GND), J2.B12 (GND), J2.SH (SHIELD), J3.A1 (GND), J3.A12 (GND), J3.B1 (GND), J3.B12 (GND), J3.SH (SHIELD), J4.4 (GND), J4.SH (Shield), J5.4, J5.8, J5.16, J6.2, J7.2, J7.6, J8.1, R3.2, R4.2, R10.2, R12.2, R14.2, R16.2, SW1.2, SW2.2, U1.1 (GND), U1.40 (GND), U1.41 (GND), U2.11 (GND), U3.3 (PGND), U3.4 (PGND), U3.5 (PGND), U3.8 (PGND), U3.9 (PGND), U3.10 (PGND), U3.12 (AGND), U4.2 (GND), U5.2 (GND), U6.10 (GND), U6.19 (CE), U7.7 (A5), U7.8 (A6), U7.9 (A7), U7.10 (GND), U7.19 (CE)
/HUB_A: J5.9, U6.12 (B6)
/HUB_B: J5.10, U6.11 (B7)
/HUB_B1: J5.3, U6.16 (B2)
/HUB_B2: J5.7, U6.13 (B5)
/HUB_C: J5.11, U7.18 (B0)
/HUB_CLK: J5.13, U7.16 (B2)
/HUB_D: J5.12, U7.17 (B1)
/HUB_G1: J5.2, U6.17 (B1)
/HUB_G2: J5.6, U6.14 (B4)
/HUB_LAT: J5.14, U7.15 (B3)
/HUB_OE: J5.15, U7.14 (B4)
/HUB_R1: J5.1, U6.18 (B0)
/HUB_R2: J5.5, U6.15 (B3)
/LED_3V3: D2.2 (A), R5.2
/MIC_SCK: J7.3, U1.5 (IO5)
/MIC_SD: J7.5, U1.7 (IO7)
/MIC_WS: J7.4, U1.6 (IO6)
/P4_5V: F2.2, J4.1 (VBUS)
/PD_CC1: J2.A5 (CC1), U2.7 (CC1)
/PD_CC2: J2.B5 (CC2), U2.6 (CC2)
/PD_CFG1: R10.1, U2.9 (CFG1)
/S3_A: U1.21 (IO13), U6.8 (A6)
/S3_B: U1.22 (IO14), U6.9 (A7)
/S3_B1: U1.17 (IO9), U6.4 (A2)
/S3_B2: U1.20 (IO12), U6.7 (A5)
/S3_BOOT: R2.2, SW2.1, U1.27 (IO0)
/S3_C: U1.8 (IO15), U7.2 (A0)
/S3_CC1: J3.A5 (CC1), R3.1
/S3_CC2: J3.B5 (CC2), R4.1
/S3_CLK: U1.10 (IO17), U7.4 (A2)
/S3_D: U1.9 (IO16), U7.3 (A1)
/S3_EN: C4.1, R1.2, SW1.1, U1.3 (EN)
/S3_G1: U1.12 (IO8), U6.3 (A1)
/S3_G2: U1.19 (IO11), U6.6 (A4)
/S3_LAT: U1.11 (IO18), U7.5 (A3)
/S3_OE: R6.2, U1.23 (IO21), U7.6 (A4)
/S3_R1: U1.4 (IO4), U6.2 (A0)
/S3_R2: U1.18 (IO10), U6.5 (A3)
/S3_UART_RX: J8.3, U1.38 (IO2)
/S3_UART_TX: J8.2, U1.39 (IO1)
/USB_DM: J3.A7 (D-), J3.B7 (D-), U1.13 (USB_D-), U4.1 (I/O1), U4.6 (I/O1)
/USB_DP: J3.A6 (D+), J3.B6 (D+), U1.14 (USB_D+), U4.3 (I/O2), U4.4 (I/O2)
/VBUS_PD: C10.1, C14.1, C15.1, C16.1, C17.1, C18.1, J2.A4 (VBUS), J2.A9 (VBUS), J2.B4 (VBUS), J2.B9 (VBUS), R13.1, U2.1 (VDD), U2.8 (VBUS), U3.2 (VIN), U3.11 (VIN)
/VIN_BARREL: F1.1, J1.1

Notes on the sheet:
5 V input (barrel), protection
3.3 V supply
USB-C power: PD 15 V request and 15 V to 5 V (not fitted in revision 1)
ESP32-S3, reset/boot, USB to the P4
LED panel: level shifting and HUB75
Microphone, P4 power, P4 UART
